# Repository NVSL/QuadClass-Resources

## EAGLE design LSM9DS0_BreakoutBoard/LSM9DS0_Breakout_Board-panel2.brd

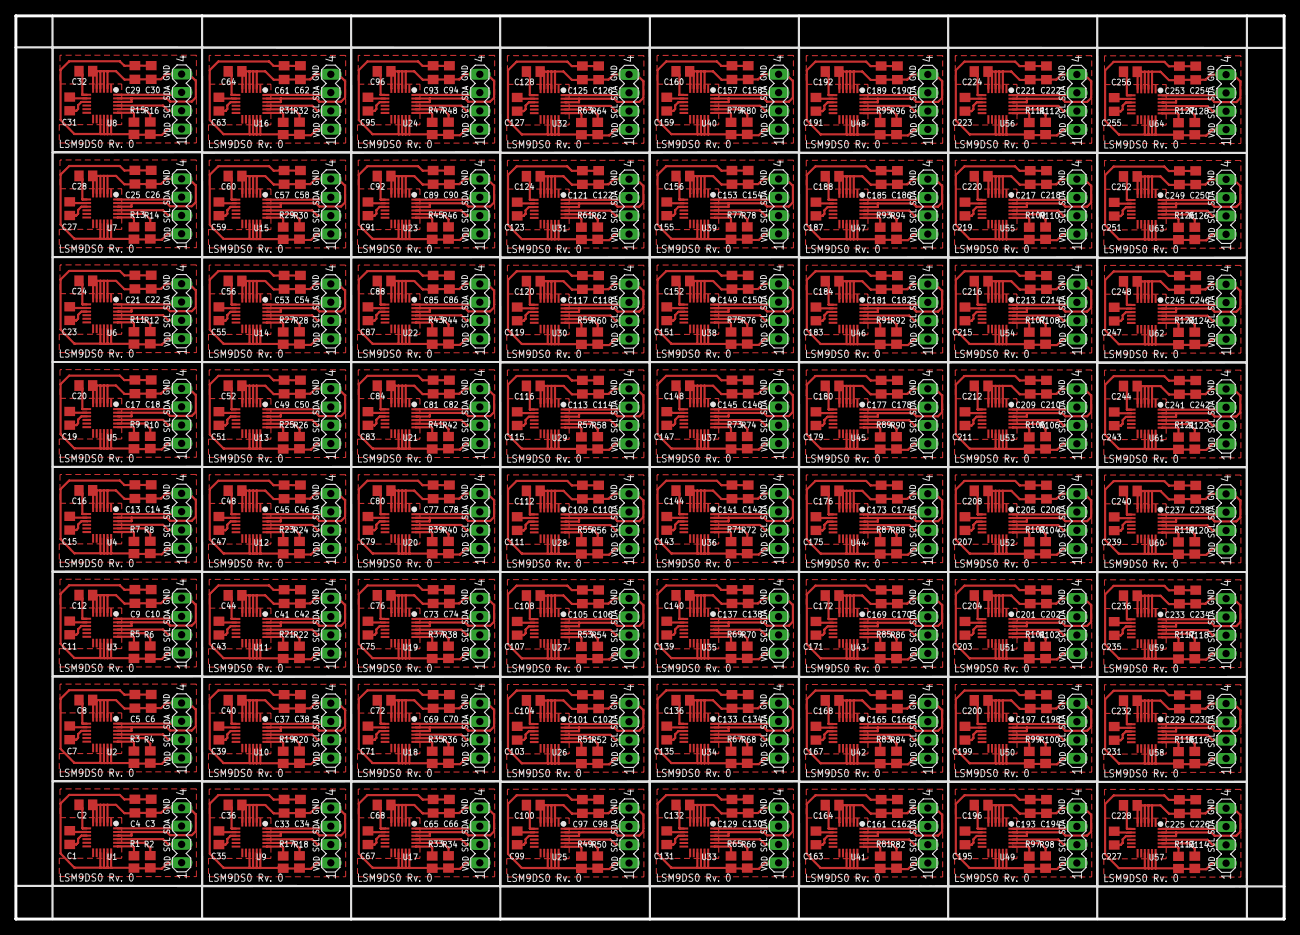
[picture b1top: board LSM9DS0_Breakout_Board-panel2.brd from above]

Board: 2 copper layers, 175.9 x 125.3 mm, 512 parts (0 on the bottom side), 576 nets.

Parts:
C1, C7, C11, C15, C19, C23, C27, C31, C35, C39, C43, C47, C51, C55, C59, C63, C67, C71, C75, C79, C83, C87, C91, C95, C99, C103, C107, C111, C115, C119, C123, C127, C131, C135, C139, C143, C147, C151, C155, C159, C163, C167, C171, C175, C179, C183, C187, C191, C195, C199, C203, C207, C211, C215, C219, C223, C227, C231, C235, C239, C243, C247, C251, C255: 0.22uF; C0805
C2, C8, C12, C16, C20, C24, C28, C32, C36, C40, C44, C48, C52, C56, C60, C64, C68, C72, C76, C80, C84, C88, C92, C96, C100, C104, C108, C112, C116, C120, C124, C128, C132, C136, C140, C144, C148, C152, C156, C160, C164, C168, C172, C176, C180, C184, C188, C192, C196, C200, C204, C208, C212, C216, C220, C224, C228, C232, C236, C240, C244, C248, C252, C256: 4.7uF; C0805
C3, C6, C10, C14, C18, C22, C26, C30, C34, C38, C42, C46, C50, C54, C58, C62, C66, C70, C74, C78, C82, C86, C90, C94, C98, C102, C106, C110, C114, C118, C122, C126, C130, C134, C138, C142, C146, C150, C154, C158, C162, C166, C170, C174, C178, C182, C186, C190, C194, C198, C202, C206, C210, C214, C218, C222, C226, C230, C234, C238, C242, C246, C250, C254: 10uF; C0805
C4, C5, C9, C13, C17, C21, C25, C29, C33, C37, C41, C45, C49, C53, C57, C61, C65, C69, C73, C77, C81, C85, C89, C93, C97, C101, C105, C109, C113, C117, C121, C125, C129, C133, C137, C141, C145, C149, C153, C157, C161, C165, C169, C173, C177, C181, C185, C189, C193, C197, C201, C205, C209, C213, C217, C221, C225, C229, C233, C237, C241, C245, C249, C253: 100nF; C0805
R1, R2, R3, R4, R5, R6, R7, R8, R9, R10, R11, R12, R13, R14, R15, R16, R17, R18, R19, R20, R21, R22, R23, R24, R25, R26, R27, R28, R29, R30, R31, R32, R33, R34, R35, R36, R37, R38, R39, R40, R41, R42, R43, R44, R45, R46, R47, R48, R49, R50, R51, R52, R53, R54, R55, R56, R57, R58, R59, R60, R61, R62, R63, R64, R65, R66, R67, R68, R69, R70, R71, R72, R73, R74, R75, R76, R77, R78, R79, R80, R81, R82, R83, R84, R85, R86, R87, R88, R89, R90, R91, R92, R93, R94, R95, R96, R97, R98, R99, R100, R101, R102, R103, R104, R105, R106, R107, R108, R109, R110, R111, R112, R113, R114, R115, R116, R117, R118, R119, R120, R121, R122, R123, R124, R125, R126, R127, R128: 10k; R0805
SV1, SV2, SV3, SV4, SV5, SV6, SV7, SV8, SV9, SV10, SV11, SV12, SV13, SV14, SV15, SV16, SV17, SV18, SV19, SV20, SV21, SV22, SV23, SV24, SV25, SV26, SV27, SV28, SV29, SV30, SV31, SV32, SV33, SV34, SV35, SV36, SV37, SV38, SV39, SV40, SV41, SV42, SV43, SV44, SV45, SV46, SV47, SV48, SV49, SV50, SV51, SV52, SV53, SV54, SV55, SV56, SV57, SV58, SV59, SV60, SV61, SV62, SV63, SV64: JP1; MA04-1
U1, U2, U3, U4, U5, U6, U7, U8, U9, U10, U11, U12, U13, U14, U15, U16, U17, U18, U19, U20, U21, U22, U23, U24, U25, U26, U27, U28, U29, U30, U31, U32, U33, U34, U35, U36, U37, U38, U39, U40, U41, U42, U43, U44, U45, U46, U47, U48, U49, U50, U51, U52, U53, U54, U55, U56, U57, U58, U59, U60, U61, U62, U63, U64: LSM9DS0; LGA-24

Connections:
GND: C2.1, C3.2, C4.2, SV1.4, U1.2, U1.3, U1.4, U1.5, U1.6, U1.22, U1.23
GND1: C5.2, C6.2, C8.1, SV2.4, U2.2, U2.3, U2.4, U2.5, U2.6, U2.22, U2.23
GND2: C9.2, C10.2, C12.1, SV3.4, U3.2, U3.3, U3.4, U3.5, U3.6, U3.22, U3.23
GND3: C13.2, C14.2, C16.1, SV4.4, U4.2, U4.3, U4.4, U4.5, U4.6, U4.22, U4.23
GND4: C17.2, C18.2, C20.1, SV5.4, U5.2, U5.3, U5.4, U5.5, U5.6, U5.22, U5.23
GND5: C21.2, C22.2, C24.1, SV6.4, U6.2, U6.3, U6.4, U6.5, U6.6, U6.22, U6.23
GND6: C25.2, C26.2, C28.1, SV7.4, U7.2, U7.3, U7.4, U7.5, U7.6, U7.22, U7.23
GND7: C29.2, C30.2, C32.1, SV8.4, U8.2, U8.3, U8.4, U8.5, U8.6, U8.22, U8.23
GND8: C33.2, C34.2, C36.1, SV9.4, U9.2, U9.3, U9.4, U9.5, U9.6, U9.22, U9.23
GND9: C37.2, C38.2, C40.1, SV10.4, U10.2, U10.3, U10.4, U10.5, U10.6, U10.22, U10.23
GND10: C41.2, C42.2, C44.1, SV11.4, U11.2, U11.3, U11.4, U11.5, U11.6, U11.22, U11.23
GND11: C45.2, C46.2, C48.1, SV12.4, U12.2, U12.3, U12.4, U12.5, U12.6, U12.22, U12.23
GND12: C49.2, C50.2, C52.1, SV13.4, U13.2, U13.3, U13.4, U13.5, U13.6, U13.22, U13.23
GND13: C53.2, C54.2, C56.1, SV14.4, U14.2, U14.3, U14.4, U14.5, U14.6, U14.22, U14.23
GND14: C57.2, C58.2, C60.1, SV15.4, U15.2, U15.3, U15.4, U15.5, U15.6, U15.22, U15.23
GND15: C61.2, C62.2, C64.1, SV16.4, U16.2, U16.3, U16.4, U16.5, U16.6, U16.22, U16.23
GND16: C65.2, C66.2, C68.1, SV17.4, U17.2, U17.3, U17.4, U17.5, U17.6, U17.22, U17.23
GND17: C69.2, C70.2, C72.1, SV18.4, U18.2, U18.3, U18.4, U18.5, U18.6, U18.22, U18.23
GND18: C73.2, C74.2, C76.1, SV19.4, U19.2, U19.3, U19.4, U19.5, U19.6, U19.22, U19.23
GND19: C77.2, C78.2, C80.1, SV20.4, U20.2, U20.3, U20.4, U20.5, U20.6, U20.22, U20.23
GND20: C81.2, C82.2, C84.1, SV21.4, U21.2, U21.3, U21.4, U21.5, U21.6, U21.22, U21.23
GND21: C85.2, C86.2, C88.1, SV22.4, U22.2, U22.3, U22.4, U22.5, U22.6, U22.22, U22.23
GND22: C89.2, C90.2, C92.1, SV23.4, U23.2, U23.3, U23.4, U23.5, U23.6, U23.22, U23.23
GND23: C93.2, C94.2, C96.1, SV24.4, U24.2, U24.3, U24.4, U24.5, U24.6, U24.22, U24.23
GND24: C97.2, C98.2, C100.1, SV25.4, U25.2, U25.3, U25.4, U25.5, U25.6, U25.22, U25.23
GND25: C101.2, C102.2, C104.1, SV26.4, U26.2, U26.3, U26.4, U26.5, U26.6, U26.22, U26.23
GND26: C105.2, C106.2, C108.1, SV27.4, U27.2, U27.3, U27.4, U27.5, U27.6, U27.22, U27.23
GND27: C109.2, C110.2, C112.1, SV28.4, U28.2, U28.3, U28.4, U28.5, U28.6, U28.22, U28.23
GND28: C113.2, C114.2, C116.1, SV29.4, U29.2, U29.3, U29.4, U29.5, U29.6, U29.22, U29.23
GND29: C117.2, C118.2, C120.1, SV30.4, U30.2, U30.3, U30.4, U30.5, U30.6, U30.22, U30.23
GND30: C121.2, C122.2, C124.1, SV31.4, U31.2, U31.3, U31.4, U31.5, U31.6, U31.22, U31.23
GND31: C125.2, C126.2, C128.1, SV32.4, U32.2, U32.3, U32.4, U32.5, U32.6, U32.22, U32.23
GND32: C129.2, C130.2, C132.1, SV33.4, U33.2, U33.3, U33.4, U33.5, U33.6, U33.22, U33.23
GND33: C133.2, C134.2, C136.1, SV34.4, U34.2, U34.3, U34.4, U34.5, U34.6, U34.22, U34.23
GND34: C137.2, C138.2, C140.1, SV35.4, U35.2, U35.3, U35.4, U35.5, U35.6, U35.22, U35.23
GND35: C141.2, C142.2, C144.1, SV36.4, U36.2, U36.3, U36.4, U36.5, U36.6, U36.22, U36.23
GND36: C145.2, C146.2, C148.1, SV37.4, U37.2, U37.3, U37.4, U37.5, U37.6, U37.22, U37.23
GND37: C149.2, C150.2, C152.1, SV38.4, U38.2, U38.3, U38.4, U38.5, U38.6, U38.22, U38.23
GND38: C153.2, C154.2, C156.1, SV39.4, U39.2, U39.3, U39.4, U39.5, U39.6, U39.22, U39.23
GND39: C157.2, C158.2, C160.1, SV40.4, U40.2, U40.3, U40.4, U40.5, U40.6, U40.22, U40.23
GND40: C161.2, C162.2, C164.1, SV41.4, U41.2, U41.3, U41.4, U41.5, U41.6, U41.22, U41.23
GND41: C165.2, C166.2, C168.1, SV42.4, U42.2, U42.3, U42.4, U42.5, U42.6, U42.22, U42.23
GND42: C169.2, C170.2, C172.1, SV43.4, U43.2, U43.3, U43.4, U43.5, U43.6, U43.22, U43.23
GND43: C173.2, C174.2, C176.1, SV44.4, U44.2, U44.3, U44.4, U44.5, U44.6, U44.22, U44.23
GND44: C177.2, C178.2, C180.1, SV45.4, U45.2, U45.3, U45.4, U45.5, U45.6, U45.22, U45.23
GND45: C181.2, C182.2, C184.1, SV46.4, U46.2, U46.3, U46.4, U46.5, U46.6, U46.22, U46.23
GND46: C185.2, C186.2, C188.1, SV47.4, U47.2, U47.3, U47.4, U47.5, U47.6, U47.22, U47.23
GND47: C189.2, C190.2, C192.1, SV48.4, U48.2, U48.3, U48.4, U48.5, U48.6, U48.22, U48.23
GND48: C193.2, C194.2, C196.1, SV49.4, U49.2, U49.3, U49.4, U49.5, U49.6, U49.22, U49.23
GND49: C197.2, C198.2, C200.1, SV50.4, U50.2, U50.3, U50.4, U50.5, U50.6, U50.22, U50.23
GND50: C201.2, C202.2, C204.1, SV51.4, U51.2, U51.3, U51.4, U51.5, U51.6, U51.22, U51.23
GND51: C205.2, C206.2, C208.1, SV52.4, U52.2, U52.3, U52.4, U52.5, U52.6, U52.22, U52.23
GND52: C209.2, C210.2, C212.1, SV53.4, U53.2, U53.3, U53.4, U53.5, U53.6, U53.22, U53.23
GND53: C213.2, C214.2, C216.1, SV54.4, U54.2, U54.3, U54.4, U54.5, U54.6, U54.22, U54.23
GND54: C217.2, C218.2, C220.1, SV55.4, U55.2, U55.3, U55.4, U55.5, U55.6, U55.22, U55.23
GND55: C221.2, C222.2, C224.1, SV56.4, U56.2, U56.3, U56.4, U56.5, U56.6, U56.22, U56.23
GND56: C225.2, C226.2, C228.1, SV57.4, U57.2, U57.3, U57.4, U57.5, U57.6, U57.22, U57.23
GND57: C229.2, C230.2, C232.1, SV58.4, U58.2, U58.3, U58.4, U58.5, U58.6, U58.22, U58.23
GND58: C233.2, C234.2, C236.1, SV59.4, U59.2, U59.3, U59.4, U59.5, U59.6, U59.22, U59.23
GND59: C237.2, C238.2, C240.1, SV60.4, U60.2, U60.3, U60.4, U60.5, U60.6, U60.22, U60.23
GND60: C241.2, C242.2, C244.1, SV61.4, U61.2, U61.3, U61.4, U61.5, U61.6, U61.22, U61.23
GND61: C245.2, C246.2, C248.1, SV62.4, U62.2, U62.3, U62.4, U62.5, U62.6, U62.22, U62.23
GND62: C249.2, C250.2, C252.1, SV63.4, U63.2, U63.3, U63.4, U63.5, U63.6, U63.22, U63.23
GND63: C253.2, C254.2, C256.1, SV64.4, U64.2, U64.3, U64.4, U64.5, U64.6, U64.22, U64.23
unnamed: C8.2, U2.7
unnamed: C7.2, U2.8
unnamed: C7.1, U2.9
unnamed: R3.1, U2.19
unnamed: R4.1, U2.20
unnamed: C12.2, U3.7
unnamed: C11.2, U3.8
unnamed: C11.1, U3.9
unnamed: R5.1, U3.19
unnamed: R6.1, U3.20
unnamed: C16.2, U4.7
unnamed: C15.2, U4.8
unnamed: C15.1, U4.9
unnamed: R7.1, U4.19
unnamed: R8.1, U4.20
unnamed: C20.2, U5.7
unnamed: C19.2, U5.8
unnamed: C19.1, U5.9
unnamed: R9.1, U5.19
unnamed: C2.2, U1.7
unnamed: C1.2, U1.8
unnamed: C1.1, U1.9
unnamed: R1.1, U1.19
unnamed: R2.1, U1.20
unnamed: R10.1, U5.20
unnamed: C24.2, U6.7
unnamed: C23.2, U6.8
unnamed: C23.1, U6.9
unnamed: R11.1, U6.19
unnamed: R12.1, U6.20
unnamed: C28.2, U7.7
unnamed: C27.2, U7.8
unnamed: C27.1, U7.9
unnamed: R13.1, U7.19
unnamed: R14.1, U7.20
unnamed: C32.2, U8.7
unnamed: C31.2, U8.8
unnamed: C31.1, U8.9
unnamed: R15.1, U8.19
unnamed: R16.1, U8.20
unnamed: C36.2, U9.7
unnamed: C35.2, U9.8
unnamed: C35.1, U9.9
unnamed: R17.1, U9.19
unnamed: R18.1, U9.20
unnamed: C40.2, U10.7
unnamed: C39.2, U10.8
unnamed: C39.1, U10.9
unnamed: R19.1, U10.19
unnamed: R20.1, U10.20
unnamed: C44.2, U11.7
unnamed: C43.2, U11.8
unnamed: C43.1, U11.9
unnamed: R21.1, U11.19
unnamed: R22.1, U11.20
unnamed: C48.2, U12.7
unnamed: C47.2, U12.8
unnamed: C47.1, U12.9
unnamed: R23.1, U12.19
unnamed: R24.1, U12.20
unnamed: C52.2, U13.7
unnamed: C51.2, U13.8
unnamed: C51.1, U13.9
unnamed: R25.1, U13.19
unnamed: R26.1, U13.20
unnamed: C56.2, U14.7
unnamed: C55.2, U14.8
unnamed: C55.1, U14.9
unnamed: R27.1, U14.19
unnamed: R28.1, U14.20
unnamed: C60.2, U15.7
unnamed: C59.2, U15.8
unnamed: C59.1, U15.9
unnamed: R29.1, U15.19
unnamed: R30.1, U15.20
unnamed: C64.2, U16.7
unnamed: C63.2, U16.8
unnamed: C63.1, U16.9
unnamed: R31.1, U16.19
unnamed: R32.1, U16.20
unnamed: C68.2, U17.7
unnamed: C67.2, U17.8
unnamed: C67.1, U17.9
unnamed: R33.1, U17.19
unnamed: R34.1, U17.20
unnamed: C72.2, U18.7
unnamed: C71.2, U18.8
unnamed: C71.1, U18.9
unnamed: R35.1, U18.19
unnamed: R36.1, U18.20
unnamed: C76.2, U19.7
unnamed: C75.2, U19.8
unnamed: C75.1, U19.9
unnamed: R37.1, U19.19
unnamed: R38.1, U19.20
unnamed: C80.2, U20.7
unnamed: C79.2, U20.8
unnamed: C79.1, U20.9
unnamed: R39.1, U20.19
unnamed: R40.1, U20.20
unnamed: C84.2, U21.7
unnamed: C83.2, U21.8
unnamed: C83.1, U21.9
unnamed: R41.1, U21.19
unnamed: R42.1, U21.20
unnamed: C88.2, U22.7
unnamed: C87.2, U22.8
unnamed: C87.1, U22.9
unnamed: R43.1, U22.19
unnamed: R44.1, U22.20
unnamed: C92.2, U23.7
unnamed: C91.2, U23.8
unnamed: C91.1, U23.9
unnamed: R45.1, U23.19
unnamed: R46.1, U23.20
unnamed: C96.2, U24.7
unnamed: C95.2, U24.8
unnamed: C95.1, U24.9
unnamed: R47.1, U24.19
unnamed: R48.1, U24.20
unnamed: C100.2, U25.7
unnamed: C99.2, U25.8
unnamed: C99.1, U25.9
unnamed: R49.1, U25.19
unnamed: R50.1, U25.20
unnamed: C104.2, U26.7
unnamed: C103.2, U26.8
unnamed: C103.1, U26.9
unnamed: R51.1, U26.19
unnamed: R52.1, U26.20
unnamed: C108.2, U27.7
unnamed: C107.2, U27.8
unnamed: C107.1, U27.9
unnamed: R53.1, U27.19
unnamed: R54.1, U27.20
unnamed: C112.2, U28.7
unnamed: C111.2, U28.8
unnamed: C111.1, U28.9
unnamed: R55.1, U28.19
unnamed: R56.1, U28.20
unnamed: C116.2, U29.7
unnamed: C115.2, U29.8
unnamed: C115.1, U29.9
unnamed: R57.1, U29.19
unnamed: R58.1, U29.20
unnamed: C120.2, U30.7
unnamed: C119.2, U30.8
unnamed: C119.1, U30.9
unnamed: R59.1, U30.19
unnamed: R60.1, U30.20
unnamed: C124.2, U31.7
unnamed: C123.2, U31.8
unnamed: C123.1, U31.9
unnamed: R61.1, U31.19
unnamed: R62.1, U31.20
unnamed: C128.2, U32.7
unnamed: C127.2, U32.8
unnamed: C127.1, U32.9
unnamed: R63.1, U32.19
unnamed: R64.1, U32.20
unnamed: C132.2, U33.7
unnamed: C131.2, U33.8
unnamed: C131.1, U33.9
unnamed: R65.1, U33.19
unnamed: R66.1, U33.20
unnamed: C136.2, U34.7
unnamed: C135.2, U34.8
unnamed: C135.1, U34.9
unnamed: R67.1, U34.19
unnamed: R68.1, U34.20
unnamed: C140.2, U35.7
unnamed: C139.2, U35.8
unnamed: C139.1, U35.9
unnamed: R69.1, U35.19
unnamed: R70.1, U35.20
unnamed: C144.2, U36.7
unnamed: C143.2, U36.8
unnamed: C143.1, U36.9
unnamed: R71.1, U36.19
unnamed: R72.1, U36.20
unnamed: C148.2, U37.7
unnamed: C147.2, U37.8
unnamed: C147.1, U37.9
unnamed: R73.1, U37.19
unnamed: R74.1, U37.20
unnamed: C152.2, U38.7
unnamed: C151.2, U38.8
unnamed: C151.1, U38.9
unnamed: R75.1, U38.19
unnamed: R76.1, U38.20
unnamed: C156.2, U39.7
unnamed: C155.2, U39.8
unnamed: C155.1, U39.9
unnamed: R77.1, U39.19
unnamed: R78.1, U39.20
unnamed: C160.2, U40.7
unnamed: C159.2, U40.8
unnamed: C159.1, U40.9
unnamed: R79.1, U40.19
unnamed: R80.1, U40.20
unnamed: C164.2, U41.7
unnamed: C163.2, U41.8
unnamed: C163.1, U41.9
unnamed: R81.1, U41.19
unnamed: R82.1, U41.20
unnamed: C168.2, U42.7
unnamed: C167.2, U42.8
unnamed: C167.1, U42.9
unnamed: R83.1, U42.19
unnamed: R84.1, U42.20
unnamed: C172.2, U43.7
unnamed: C171.2, U43.8
unnamed: C171.1, U43.9
unnamed: R85.1, U43.19
unnamed: R86.1, U43.20
unnamed: C176.2, U44.7
unnamed: C175.2, U44.8
unnamed: C175.1, U44.9
unnamed: R87.1, U44.19
unnamed: R88.1, U44.20
unnamed: C180.2, U45.7
unnamed: C179.2, U45.8
unnamed: C179.1, U45.9
unnamed: R89.1, U45.19
unnamed: R90.1, U45.20
unnamed: C184.2, U46.7
unnamed: C183.2, U46.8
unnamed: C183.1, U46.9
unnamed: R91.1, U46.19
unnamed: R92.1, U46.20
unnamed: C188.2, U47.7
unnamed: C187.2, U47.8
unnamed: C187.1, U47.9
unnamed: R93.1, U47.19
unnamed: R94.1, U47.20
unnamed: C192.2, U48.7
unnamed: C191.2, U48.8
unnamed: C191.1, U48.9
unnamed: R95.1, U48.19
unnamed: R96.1, U48.20
unnamed: C196.2, U49.7
unnamed: C195.2, U49.8
unnamed: C195.1, U49.9
unnamed: R97.1, U49.19
unnamed: R98.1, U49.20
unnamed: C200.2, U50.7
unnamed: C199.2, U50.8
unnamed: C199.1, U50.9
unnamed: R99.1, U50.19
unnamed: R100.1, U50.20
unnamed: C204.2, U51.7
unnamed: C203.2, U51.8
unnamed: C203.1, U51.9
unnamed: R101.1, U51.19
unnamed: R102.1, U51.20
unnamed: C208.2, U52.7
unnamed: C207.2, U52.8
unnamed: C207.1, U52.9
unnamed: R103.1, U52.19
unnamed: R104.1, U52.20
unnamed: C212.2, U53.7
unnamed: C211.2, U53.8
unnamed: C211.1, U53.9
unnamed: R105.1, U53.19
unnamed: R106.1, U53.20
unnamed: C216.2, U54.7
unnamed: C215.2, U54.8
unnamed: C215.1, U54.9
unnamed: R107.1, U54.19
unnamed: R108.1, U54.20
unnamed: C220.2, U55.7
unnamed: C219.2, U55.8
unnamed: C219.1, U55.9
unnamed: R109.1, U55.19
unnamed: R110.1, U55.20
unnamed: C224.2, U56.7
unnamed: C223.2, U56.8
unnamed: C223.1, U56.9
unnamed: R111.1, U56.19
unnamed: R112.1, U56.20
unnamed: C228.2, U57.7
unnamed: C227.2, U57.8
unnamed: C227.1, U57.9
unnamed: R113.1, U57.19
unnamed: R114.1, U57.20
unnamed: C232.2, U58.7
unnamed: C231.2, U58.8
unnamed: C231.1, U58.9
unnamed: R115.1, U58.19
unnamed: R116.1, U58.20
unnamed: C236.2, U59.7
unnamed: C235.2, U59.8
unnamed: C235.1, U59.9
unnamed: R117.1, U59.19
unnamed: R118.1, U59.20
unnamed: C240.2, U60.7
unnamed: C239.2, U60.8
unnamed: C239.1, U60.9
unnamed: R119.1, U60.19
unnamed: R120.1, U60.20
unnamed: C244.2, U61.7
unnamed: C243.2, U61.8
unnamed: C243.1, U61.9
unnamed: R121.1, U61.19
unnamed: R122.1, U61.20
unnamed: C248.2, U62.7
unnamed: C247.2, U62.8
unnamed: C247.1, U62.9
unnamed: R123.1, U62.19
unnamed: R124.1, U62.20
unnamed: C252.2, U63.7
unnamed: C251.2, U63.8
unnamed: C251.1, U63.9
unnamed: R125.1, U63.19
unnamed: R126.1, U63.20
unnamed: C256.2, U64.7
unnamed: C255.2, U64.8
unnamed: C255.1, U64.9
unnamed: R127.1, U64.19
unnamed: R128.1, U64.20
SCL: SV1.2, U1.21
SCL1: SV2.2, U2.21
SCL2: SV3.2, U3.21
SCL3: SV4.2, U4.21
SCL4: SV5.2, U5.21
SCL5: SV6.2, U6.21
SCL6: SV7.2, U7.21
SCL7: SV8.2, U8.21
SCL8: SV9.2, U9.21
SCL9: SV10.2, U10.21
SCL10: SV11.2, U11.21
SCL11: SV12.2, U12.21
SCL12: SV13.2, U13.21
SCL13: SV14.2, U14.21
SCL14: SV15.2, U15.21
SCL15: SV16.2, U16.21
SCL16: SV17.2, U17.21
SCL17: SV18.2, U18.21
SCL18: SV19.2, U19.21
SCL19: SV20.2, U20.21
SCL20: SV21.2, U21.21
SCL21: SV22.2, U22.21
SCL22: SV23.2, U23.21
SCL23: SV24.2, U24.21
SCL24: SV25.2, U25.21
SCL25: SV26.2, U26.21
SCL26: SV27.2, U27.21
SCL27: SV28.2, U28.21
SCL28: SV29.2, U29.21
SCL29: SV30.2, U30.21
SCL30: SV31.2, U31.21
SCL31: SV32.2, U32.21
SCL32: SV33.2, U33.21
SCL33: SV34.2, U34.21
SCL34: SV35.2, U35.21
SCL35: SV36.2, U36.21
SCL36: SV37.2, U37.21
SCL37: SV38.2, U38.21
SCL38: SV39.2, U39.21
SCL39: SV40.2, U40.21
SCL40: SV41.2, U41.21
SCL41: SV42.2, U42.21
SCL42: SV43.2, U43.21
SCL43: SV44.2, U44.21
SCL44: SV45.2, U45.21
SCL45: SV46.2, U46.21
SCL46: SV47.2, U47.21
SCL47: SV48.2, U48.21
SCL48: SV49.2, U49.21
SCL49: SV50.2, U50.21
SCL50: SV51.2, U51.21
SCL51: SV52.2, U52.21
SCL52: SV53.2, U53.21
SCL53: SV54.2, U54.21
SCL54: SV55.2, U55.21
SCL55: SV56.2, U56.21
SCL56: SV57.2, U57.21
SCL57: SV58.2, U58.21
SCL58: SV59.2, U59.21
SCL59: SV60.2, U60.21
SCL60: SV61.2, U61.21
SCL61: SV62.2, U62.21
SCL62: SV63.2, U63.21
SCL63: SV64.2, U64.21
SDA: SV1.3, U1.24
SDA1: SV2.3, U2.24
SDA2: SV3.3, U3.24
SDA3: SV4.3, U4.24
SDA4: SV5.3, U5.24
SDA5: SV6.3, U6.24
SDA6: SV7.3, U7.24
SDA7: SV8.3, U8.24
SDA8: SV9.3, U9.24
SDA9: SV10.3, U10.24
SDA10: SV11.3, U11.24
SDA11: SV12.3, U12.24
SDA12: SV13.3, U13.24
SDA13: SV14.3, U14.24
SDA14: SV15.3, U15.24
SDA15: SV16.3, U16.24
SDA16: SV17.3, U17.24
SDA17: SV18.3, U18.24
SDA18: SV19.3, U19.24
SDA19: SV20.3, U20.24
SDA20: SV21.3, U21.24
SDA21: SV22.3, U22.24
SDA22: SV23.3, U23.24
SDA23: SV24.3, U24.24
SDA24: SV25.3, U25.24
SDA25: SV26.3, U26.24
SDA26: SV27.3, U27.24
SDA27: SV28.3, U28.24
SDA28: SV29.3, U29.24
SDA29: SV30.3, U30.24
SDA30: SV31.3, U31.24
SDA31: SV32.3, U32.24
SDA32: SV33.3, U33.24
SDA33: SV34.3, U34.24
SDA34: SV35.3, U35.24
SDA35: SV36.3, U36.24
SDA36: SV37.3, U37.24
SDA37: SV38.3, U38.24
SDA38: SV39.3, U39.24
SDA39: SV40.3, U40.24
SDA40: SV41.3, U41.24
SDA41: SV42.3, U42.24
SDA42: SV43.3, U43.24
SDA43: SV44.3, U44.24
SDA44: SV45.3, U45.24
SDA45: SV46.3, U46.24
SDA46: SV47.3, U47.24
SDA47: SV48.3, U48.24
SDA48: SV49.3, U49.24
SDA49: SV50.3, U50.24
SDA50: SV51.3, U51.24
SDA51: SV52.3, U52.24
SDA52: SV53.3, U53.24
SDA53: SV54.3, U54.24
SDA54: SV55.3, U55.24
SDA55: SV56.3, U56.24
SDA56: SV57.3, U57.24
SDA57: SV58.3, U58.24
SDA58: SV59.3, U59.24
SDA59: SV60.3, U60.24
SDA60: SV61.3, U61.24
SDA61: SV62.3, U62.24
SDA62: SV63.3, U63.24
SDA63: SV64.3, U64.24
VDD: C3.1, C4.1, R1.2, R2.2, SV1.1, U1.15, U1.16, U1.17, U1.18
VDD1: C5.1, C6.1, R3.2, R4.2, SV2.1, U2.15, U2.16, U2.17, U2.18
VDD2: C9.1, C10.1, R5.2, R6.2, SV3.1, U3.15, U3.16, U3.17, U3.18
VDD3: C13.1, C14.1, R7.2, R8.2, SV4.1, U4.15, U4.16, U4.17, U4.18
VDD4: C17.1, C18.1, R9.2, R10.2, SV5.1, U5.15, U5.16, U5.17, U5.18
VDD5: C21.1, C22.1, R11.2, R12.2, SV6.1, U6.15, U6.16, U6.17, U6.18
VDD6: C25.1, C26.1, R13.2, R14.2, SV7.1, U7.15, U7.16, U7.17, U7.18
VDD7: C29.1, C30.1, R15.2, R16.2, SV8.1, U8.15, U8.16, U8.17, U8.18
VDD8: C33.1, C34.1, R17.2, R18.2, SV9.1, U9.15, U9.16, U9.17, U9.18
VDD9: C37.1, C38.1, R19.2, R20.2, SV10.1, U10.15, U10.16, U10.17, U10.18
VDD10: C41.1, C42.1, R21.2, R22.2, SV11.1, U11.15, U11.16, U11.17, U11.18
VDD11: C45.1, C46.1, R23.2, R24.2, SV12.1, U12.15, U12.16, U12.17, U12.18
VDD12: C49.1, C50.1, R25.2, R26.2, SV13.1, U13.15, U13.16, U13.17, U13.18
VDD13: C53.1, C54.1, R27.2, R28.2, SV14.1, U14.15, U14.16, U14.17, U14.18
VDD14: C57.1, C58.1, R29.2, R30.2, SV15.1, U15.15, U15.16, U15.17, U15.18
VDD15: C61.1, C62.1, R31.2, R32.2, SV16.1, U16.15, U16.16, U16.17, U16.18
VDD16: C65.1, C66.1, R33.2, R34.2, SV17.1, U17.15, U17.16, U17.17, U17.18
VDD17: C69.1, C70.1, R35.2, R36.2, SV18.1, U18.15, U18.16, U18.17, U18.18
VDD18: C73.1, C74.1, R37.2, R38.2, SV19.1, U19.15, U19.16, U19.17, U19.18
VDD19: C77.1, C78.1, R39.2, R40.2, SV20.1, U20.15, U20.16, U20.17, U20.18
VDD20: C81.1, C82.1, R41.2, R42.2, SV21.1, U21.15, U21.16, U21.17, U21.18
VDD21: C85.1, C86.1, R43.2, R44.2, SV22.1, U22.15, U22.16, U22.17, U22.18
VDD22: C89.1, C90.1, R45.2, R46.2, SV23.1, U23.15, U23.16, U23.17, U23.18
VDD23: C93.1, C94.1, R47.2, R48.2, SV24.1, U24.15, U24.16, U24.17, U24.18
VDD24: C97.1, C98.1, R49.2, R50.2, SV25.1, U25.15, U25.16, U25.17, U25.18
VDD25: C101.1, C102.1, R51.2, R52.2, SV26.1, U26.15, U26.16, U26.17, U26.18
VDD26: C105.1, C106.1, R53.2, R54.2, SV27.1, U27.15, U27.16, U27.17, U27.18
VDD27: C109.1, C110.1, R55.2, R56.2, SV28.1, U28.15, U28.16, U28.17, U28.18
VDD28: C113.1, C114.1, R57.2, R58.2, SV29.1, U29.15, U29.16, U29.17, U29.18
VDD29: C117.1, C118.1, R59.2, R60.2, SV30.1, U30.15, U30.16, U30.17, U30.18
VDD30: C121.1, C122.1, R61.2, R62.2, SV31.1, U31.15, U31.16, U31.17, U31.18
VDD31: C125.1, C126.1, R63.2, R64.2, SV32.1, U32.15, U32.16, U32.17, U32.18
VDD32: C129.1, C130.1, R65.2, R66.2, SV33.1, U33.15, U33.16, U33.17, U33.18
VDD33: C133.1, C134.1, R67.2, R68.2, SV34.1, U34.15, U34.16, U34.17, U34.18
VDD34: C137.1, C138.1, R69.2, R70.2, SV35.1, U35.15, U35.16, U35.17, U35.18
VDD35: C141.1, C142.1, R71.2, R72.2, SV36.1, U36.15, U36.16, U36.17, U36.18
VDD36: C145.1, C146.1, R73.2, R74.2, SV37.1, U37.15, U37.16, U37.17, U37.18
VDD37: C149.1, C150.1, R75.2, R76.2, SV38.1, U38.15, U38.16, U38.17, U38.18
VDD38: C153.1, C154.1, R77.2, R78.2, SV39.1, U39.15, U39.16, U39.17, U39.18
VDD39: C157.1, C158.1, R79.2, R80.2, SV40.1, U40.15, U40.16, U40.17, U40.18
VDD40: C161.1, C162.1, R81.2, R82.2, SV41.1, U41.15, U41.16, U41.17, U41.18
VDD41: C165.1, C166.1, R83.2, R84.2, SV42.1, U42.15, U42.16, U42.17, U42.18
VDD42: C169.1, C170.1, R85.2, R86.2, SV43.1, U43.15, U43.16, U43.17, U43.18
VDD43: C173.1, C174.1, R87.2, R88.2, SV44.1, U44.15, U44.16, U44.17, U44.18
VDD44: C177.1, C178.1, R89.2, R90.2, SV45.1, U45.15, U45.16, U45.17, U45.18
VDD45: C181.1, C182.1, R91.2, R92.2, SV46.1, U46.15, U46.16, U46.17, U46.18
VDD46: C185.1, C186.1, R93.2, R94.2, SV47.1, U47.15, U47.16, U47.17, U47.18
VDD47: C189.1, C190.1, R95.2, R96.2, SV48.1, U48.15, U48.16, U48.17, U48.18
VDD48: C193.1, C194.1, R97.2, R98.2, SV49.1, U49.15, U49.16, U49.17, U49.18
VDD49: C197.1, C198.1, R99.2, R100.2, SV50.1, U50.15, U50.16, U50.17, U50.18
VDD50: C201.1, C202.1, R101.2, R102.2, SV51.1, U51.15, U51.16, U51.17, U51.18
VDD51: C205.1, C206.1, R103.2, R104.2, SV52.1, U52.15, U52.16, U52.17, U52.18
VDD52: C209.1, C210.1, R105.2, R106.2, SV53.1, U53.15, U53.16, U53.17, U53.18
VDD53: C213.1, C214.1, R107.2, R108.2, SV54.1, U54.15, U54.16, U54.17, U54.18
VDD54: C217.1, C218.1, R109.2, R110.2, SV55.1, U55.15, U55.16, U55.17, U55.18
VDD55: C221.1, C222.1, R111.2, R112.2, SV56.1, U56.15, U56.16, U56.17, U56.18
VDD56: C225.1, C226.1, R113.2, R114.2, SV57.1, U57.15, U57.16, U57.17, U57.18
VDD57: C229.1, C230.1, R115.2, R116.2, SV58.1, U58.15, U58.16, U58.17, U58.18
VDD58: C233.1, C234.1, R117.2, R118.2, SV59.1, U59.15, U59.16, U59.17, U59.18
VDD59: C237.1, C238.1, R119.2, R120.2, SV60.1, U60.15, U60.16, U60.17, U60.18
VDD60: C241.1, C242.1, R121.2, R122.2, SV61.1, U61.15, U61.16, U61.17, U61.18
VDD61: C245.1, C246.1, R123.2, R124.2, SV62.1, U62.15, U62.16, U62.17, U62.18
VDD62: C249.1, C250.1, R125.2, R126.2, SV63.1, U63.15, U63.16, U63.17, U63.18
VDD63: C253.1, C254.1, R127.2, R128.2, SV64.1, U64.15, U64.16, U64.17, U64.18

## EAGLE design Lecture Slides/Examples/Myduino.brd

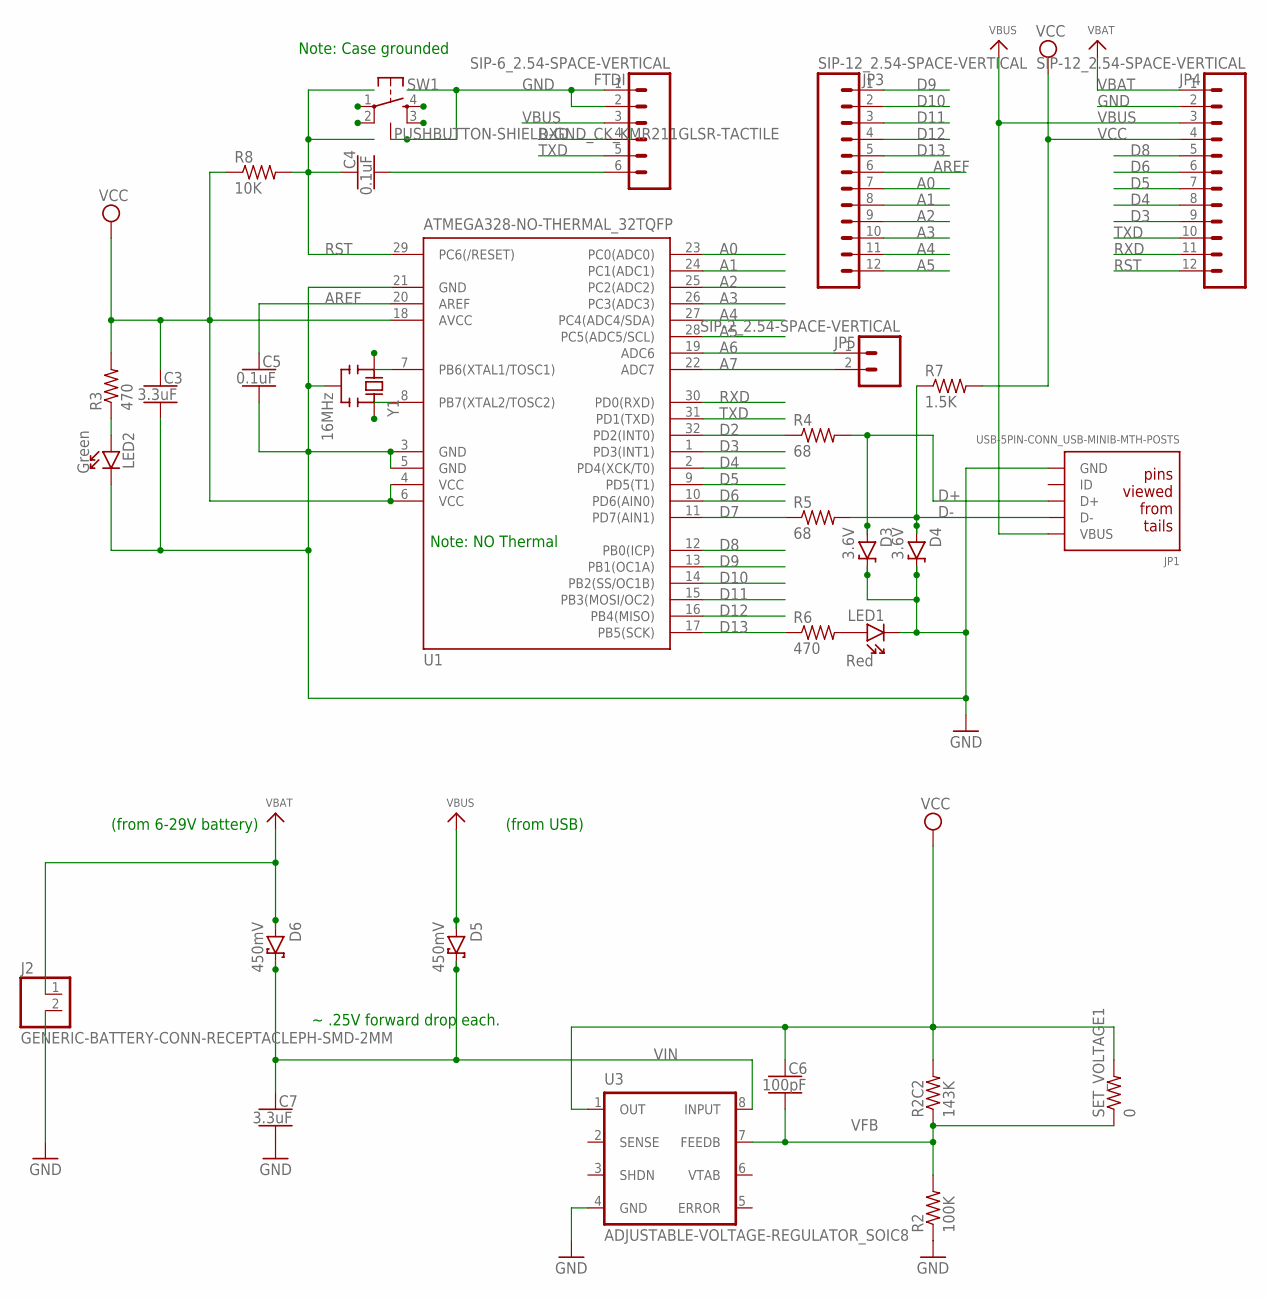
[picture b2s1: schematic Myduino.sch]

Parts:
C3, C7: 3.3uF; CAPC2012X140_HS
C4, C5: 0.1uF; CAPRB500W53L600T350H600_HS
C6: 100pF; CAPRB500W53L550T250H550_HS
D3, D4: 3.6V; DIOAD1660W102L890D370_HS
D5, D6: 450mV; DIOAD1125W78L520D270_HS
FTDI: SIP-6_2.54-SPACE-VERTICAL; HDRV6W63P254_6X1_1524X254H838; MPN TSW-150-07-T-S
J2: GENERIC-BATTERY-CONN-RECEPTACLEPH-SMD-2MM; JST_S2B-PH-SM4-TB; MPN S2B-PH-SM4-TB(LF)(SN)
JP1: USB-5PIN-CONN_USB-MINIB-MTH-POSTS; FCI_10033526; MPN 10033526-N3212MLF
JP3, JP4: SIP-12_2.54-SPACE-VERTICAL; HDRV12W63P254_12X1_3048X254H838; MPN TSW-150-07-T-S
JP5: SIP-2_2.54-SPACE-VERTICAL; HDRV2W63P254_2X1_508X254H838; MPN TSW-150-07-T-S
LED1: Red; LEDRD250W50D400H640_HS
LED2: Green; LEDRD250W50D400H640_HS
R2: 100K; RESAD1160W55L680D260_HS
R2C2: 143K; RESAD1160W55L680D260_HS
R3, R6: 470; RESAD770W45L370D210_HS
R4, R5: 68; RESAD770W45L370D210_HS
R7: 1.5K; RESAD770W45L370D210_HS
R8: 10K; RESAD770W45L370D210_HS
SET_VOLTAGE1: 0; RESAD770W45L370D210_HS
SW1: PUSHBUTTON-SHIELD-GND_CK_KMR211GLSR-TACTILE; CK_KMR211GLSR; MPN KMR211GLFS
U1: ATMEGA328-NO-THERMAL_32TQFP; QFP80P900X900X120-32L30HS; MPN ATMEGA328-AU
U3: ADJUSTABLE-VOLTAGE-REGULATOR_SOIC8; SOIC127P600X175-8L86HS; MPN MIC2951-03YM
Y1: 16MHz; MURATA_CTLS8_X_SERIES_HS

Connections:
A0: JP3.7, U1.23 (PC0(ADC0))
A1: JP3.8, U1.24 (PC1(ADC1))
A2: JP3.9, U1.25 (PC2(ADC2))
A3: JP3.10, U1.26 (PC3(ADC3))
A4: JP3.11, U1.27 (PC4(ADC4/SDA))
A5: JP3.12, U1.28 (PC5(ADC5/SCL))
A6: JP5.1, U1.19 (ADC6)
A7: JP5.2, U1.22 (ADC7)
AREF: C5.1, JP3.6, U1.20 (AREF)
D2: R4.1, U1.32 (PD2(INT0))
D3: JP4.9, U1.1 (PD3(INT1))
D4: JP4.8, U1.2 (PD4(XCK/T0))
D5: JP4.7, U1.9 (PD5(T1))
D6: JP4.6, U1.10 (PD6(AIN0))
D7: R5.1, U1.11 (PD7(AIN1))
D8: JP4.5, U1.12 (PB0(ICP))
D9: JP3.1, U1.13 (PB1(OC1A))
D10: JP3.2, U1.14 (PB2(SS/OC1B))
D11: JP3.3, U1.15 (PB3(MOSI/OC2))
D12: JP3.4, U1.16 (PB4(MISO))
D13: JP3.5, R6.1, U1.17 (PB5(SCK))
D+: D3.A, JP1.3 (D+), R4.2
D-: D4.A, JP1.2 (D-), R5.2, R7.1
DTR/RTS: C4.2, FTDI.6
GND: C3.2, C5.2, C7.2, D3.C, D4.C, FTDI.1, FTDI.2, J2.2, JP1.5 (GND), JP4.2, LED1.C, LED2.C, R2.1, SW1.1, SW1.4, SW1.5, U1.3 (GND), U1.5 (GND), U1.21 (GND), U3.4 (GND), Y1.2 (GND)
unnamed: LED1.A, R6.2
unnamed: U1.8 (PB7(XTAL2/TOSC2)), Y1.1 (OSC2)
unnamed: U1.7 (PB6(XTAL1/TOSC1)), Y1.3 (OSC1)
unnamed: LED2.A, R3.1
RST: C4.1, JP4.12, R8.2, SW1.2, SW1.3, U1.29 (PC6(/RESET))
RXD: FTDI.4, JP4.11, U1.30 (PD0(RXD))
TXD: FTDI.5, JP4.10, U1.31 (PD1(TXD))
VBAT: D6.A, J2.1, JP4.1
VBUS: D5.A, FTDI.3, JP1.1 (VBUS), JP4.3
VCC: C3.1, C6.1, JP4.4, R2C2.2, R3.2, R7.2, R8.1, SET_VOLTAGE1.2, U1.4 (VCC), U1.6 (VCC), U1.18 (AVCC), U3.1 (OUT)
VFB: C6.2, R2.2, R2C2.1, SET_VOLTAGE1.1, U3.7 (FEEDB)
VIN: C7.1, D5.C, D6.C, U3.8 (INPUT)

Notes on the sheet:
(from USB)
(from 6-29V battery)
Note: Case grounded
~ .25V forward drop each.
Note: NO Thermal

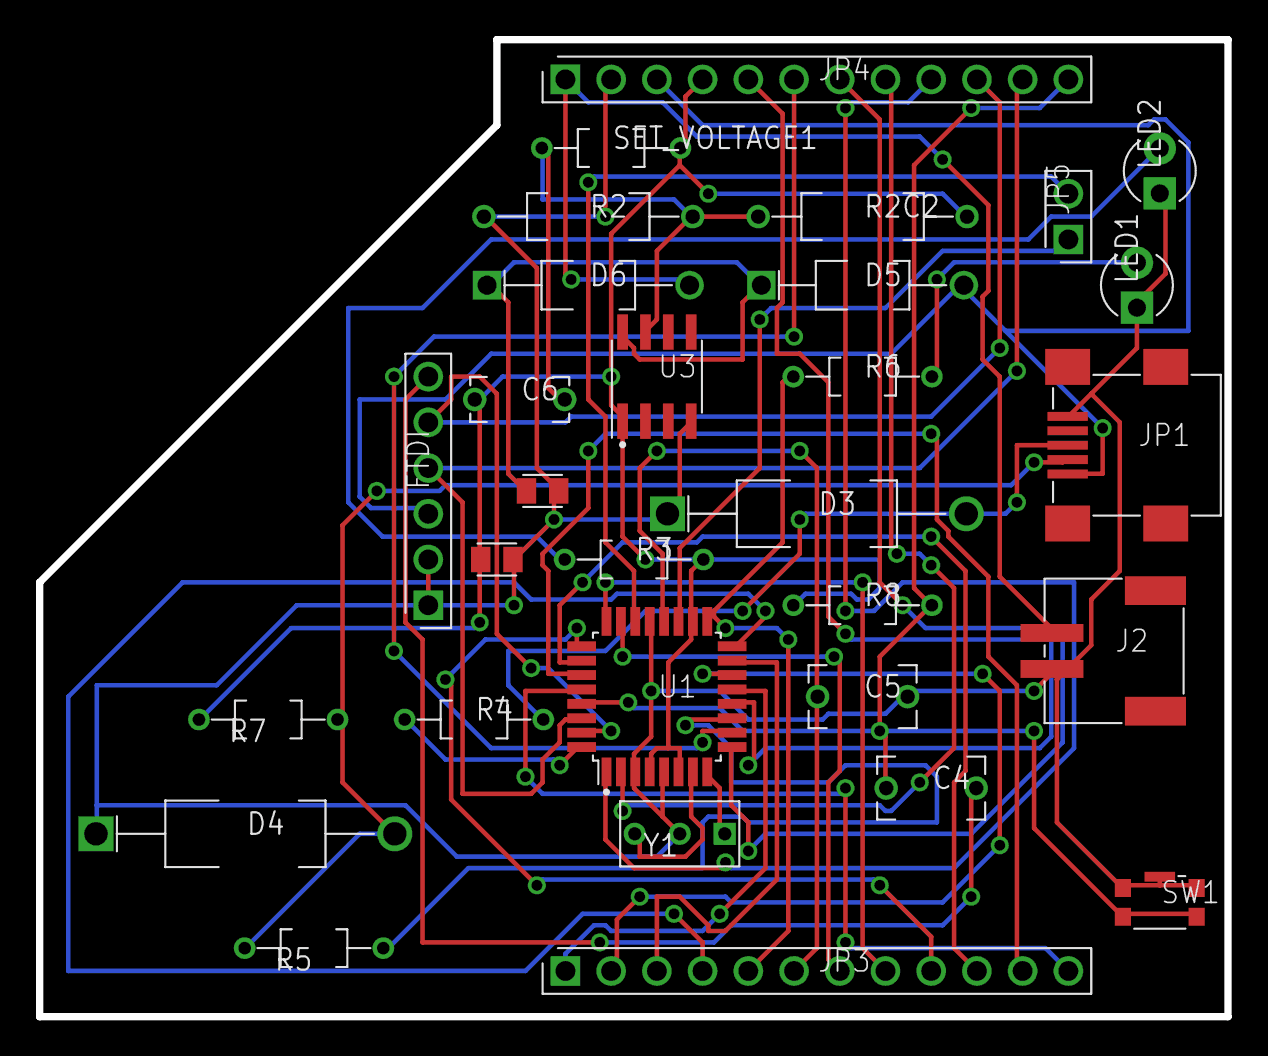
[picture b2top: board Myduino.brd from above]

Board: 2 copper layers, 66.0 x 54.3 mm, 30 parts (0 on the bottom side), 37 nets.

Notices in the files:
parts and their libraries:
microbuilder: This work is placed in the public domain, and may be freely used for commercial and non-commercial work with the following conditions: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
